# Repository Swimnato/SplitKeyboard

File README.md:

# SplitKeyboard
Split keyboard with rotary encoder using the Nice!Nano V2

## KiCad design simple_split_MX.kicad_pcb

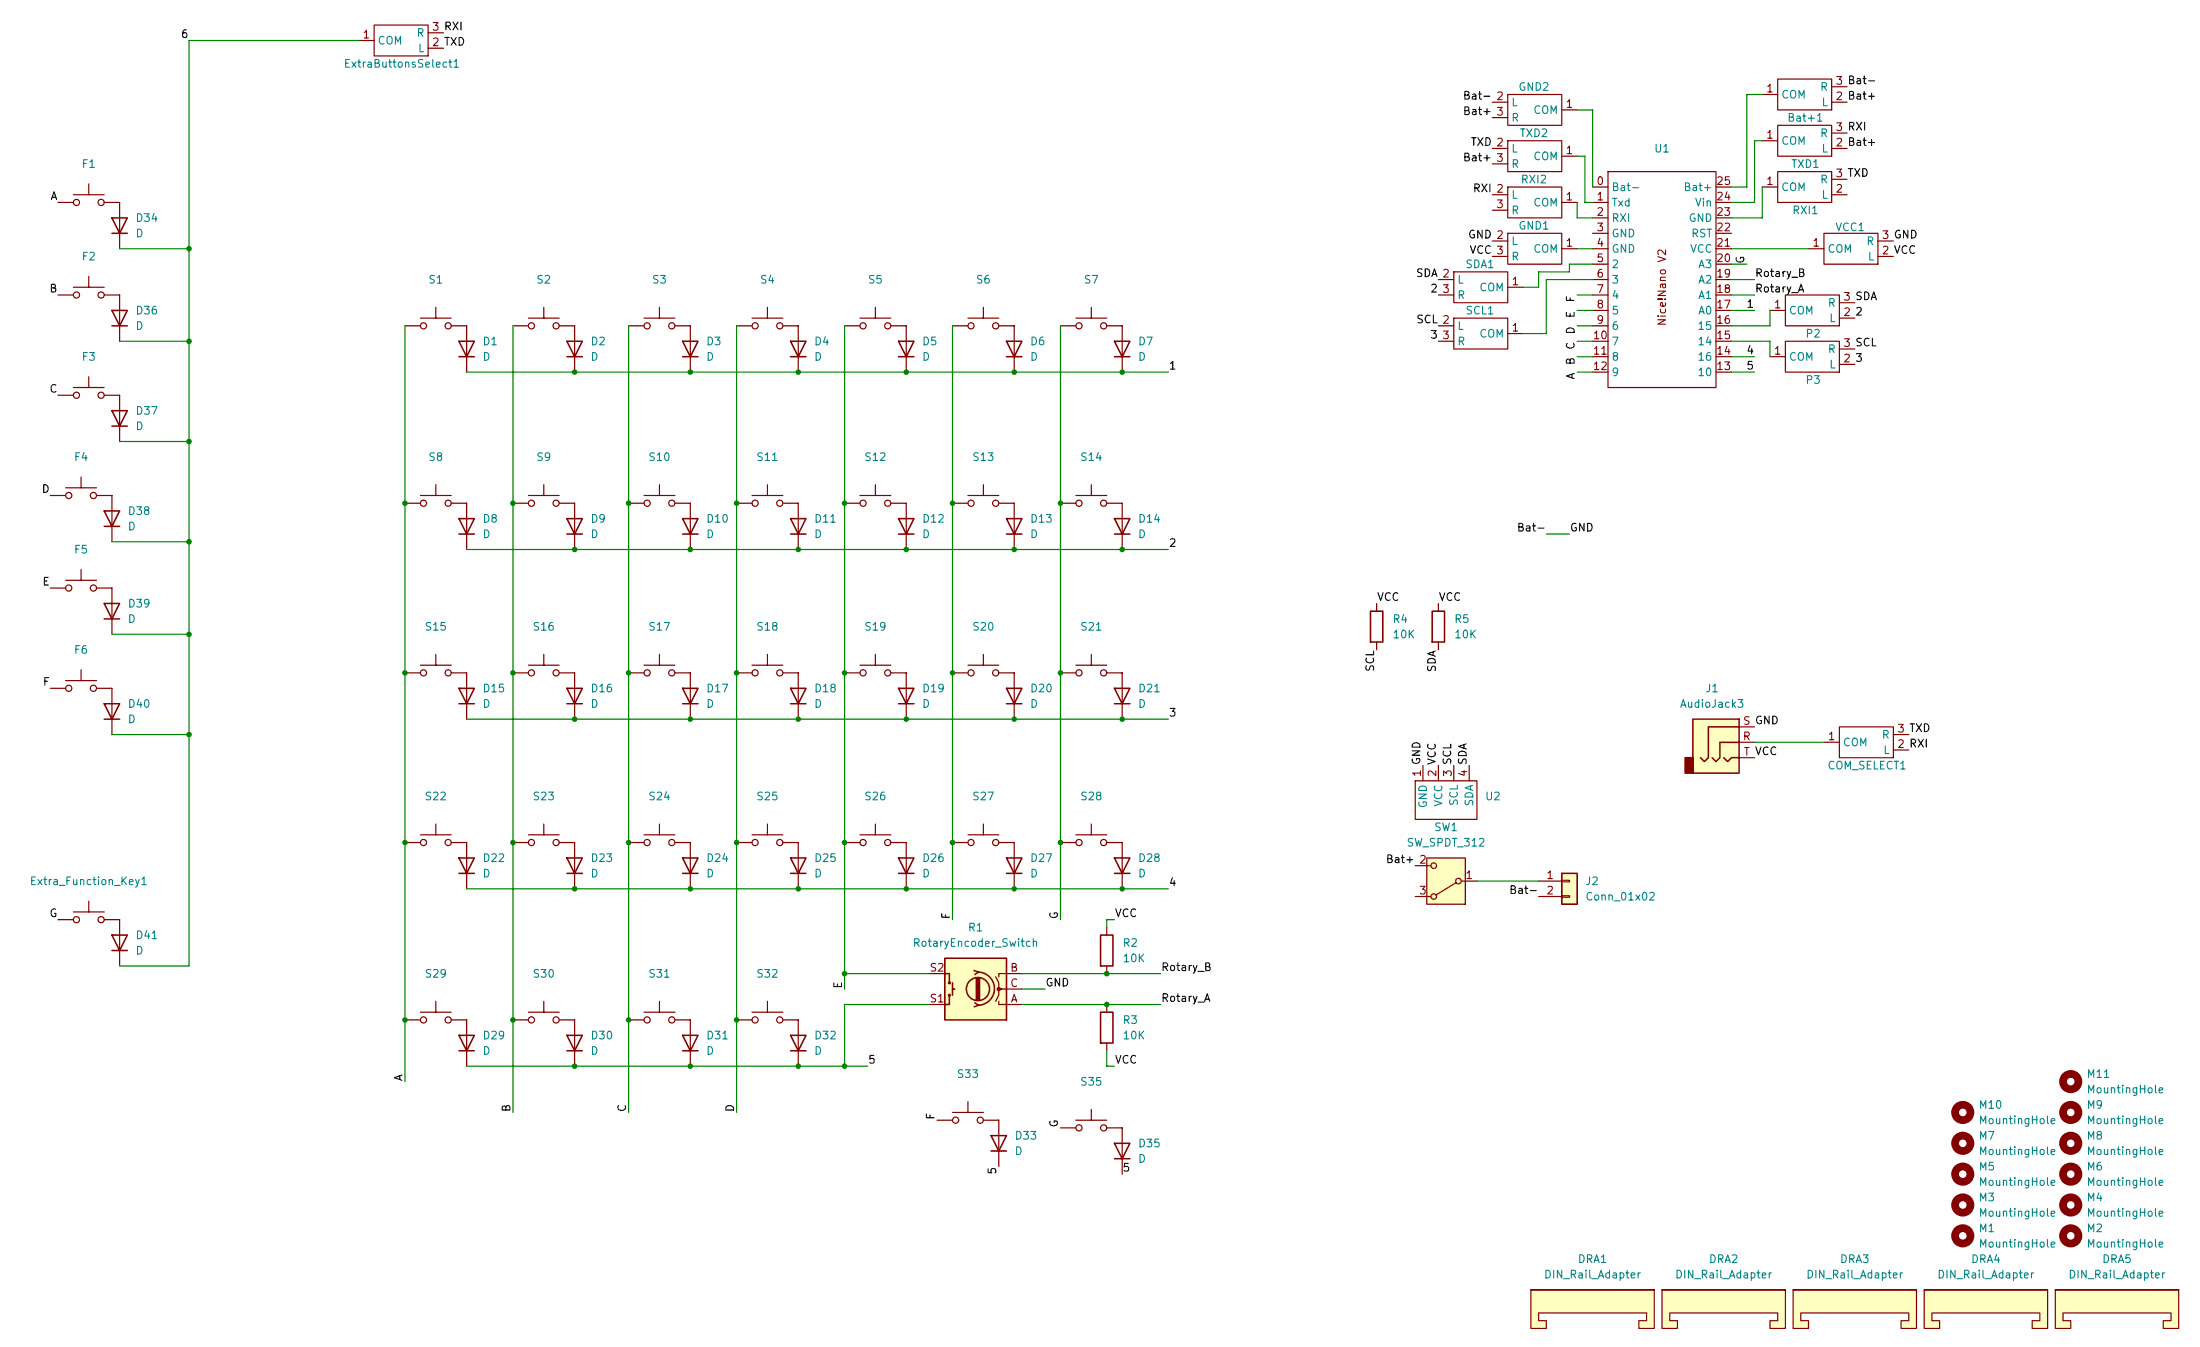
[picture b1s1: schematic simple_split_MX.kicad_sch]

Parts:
Bat+1: Side Indicator - Improved
COM_SELECT1: Side Indicator - Improved
D1, D2, D3, D4, D5, D6, D7, D8, D9, D10, D11, D12, D13, D14, D15, D16, D17, D18, D19, D20, D21, D22, D23, D24, D25, D26, D27, D28, D29, D30, D31, D32, D33, D34, D35, D36, D37, D38, D39, D40, D41: D; reversable_diode
DRA1, DRA2, DRA3, DRA4, DRA5: DIN_Rail_Adapter; Stabilizer_MX_2u
ExtraButtonsSelect1: Side Indicator - Improved
Extra_Function_Key1: Kailh_socket_MX_reversible
F1, F2, F3, F4, F5, F6: Kailh_socket_MX_reversible
GND1, GND2: Side Indicator - Improved
J1: AudioJack3; Jack_3.5mm_CUI_SJ1-3533NG_Horizontal Reversable
J2: Conn_01x02; JST_EH_S2B-EH_1x02_P2.50mm_Horizontal
M1, M2, M3, M4, M5, M6, M7, M8, M9, M10, M11: MountingHole; MountingHole_2.2mm_M2
P2, P3: Side Indicator - Improved
R1: RotaryEncoder_Switch; RotaryEncoder_Alps_EC11E-Switch_Vertical_H20mm
R2, R3, R4, R5: 10K; R_Axial_DIN0204_L3.6mm_D1.6mm_P7.62mm_Horizontal
RXI1, RXI2: Side Indicator - Improved
S1, S2, S3, S4, S5, S6, S7, S8, S9, S10, S11, S12, S13, S14, S15, S16, S17, S18, S19, S20, S21, S22, S23, S24, S25, S26, S27, S28, S29, S30, S31, S32, S33, S35: Kailh_socket_MX_reversible
SCL1: Side Indicator - Improved
SDA1: Side Indicator - Improved
SW1: SW_SPDT_312; SW_Slide_SPDT_Angled_CK_OS102011MA1Q
TXD1, TXD2: Side Indicator - Improved
U1: Nice!NanoV2
U2: Screen
VCC1: Side Indicator - Improved

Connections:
/1: D1.1 (K), D2.1 (K), D3.1 (K), D4.1 (K), D5.1 (K), D6.1 (K), D7.1 (K), U1.17 (A0)
/2: D8.1 (K), D9.1 (K), D10.1 (K), D11.1 (K), D12.1 (K), D13.1 (K), D14.1 (K), P2.2 (L), SDA1.3 (R)
/3: D15.1 (K), D16.1 (K), D17.1 (K), D18.1 (K), D19.1 (K), D20.1 (K), D21.1 (K), P3.2 (L), SCL1.3 (R)
/4: D22.1 (K), D23.1 (K), D24.1 (K), D25.1 (K), D26.1 (K), D27.1 (K), D28.1 (K), U1.14 (16)
/5: D29.1 (K), D30.1 (K), D31.1 (K), D32.1 (K), D33.1 (K), D35.1 (K), R1.S1, U1.13 (10)
/6: D34.1 (K), D36.1 (K), D37.1 (K), D38.1 (K), D39.1 (K), D40.1 (K), D41.1 (K), ExtraButtonsSelect1.1 (COM)
/A: F1.1 (A), S1.1 (A), S8.1 (A), S15.1 (A), S22.1 (A), S29.1 (A), U1.12 (9)
/B: F2.1 (A), S2.1 (A), S9.1 (A), S16.1 (A), S23.1 (A), S30.1 (A), U1.11 (8)
/Bat+: Bat+1.2 (L), GND2.3 (R), SW1.2 (C), TXD1.2 (L), TXD2.3 (R)
/Bat-: Bat+1.3 (R), GND1.2 (L), GND2.2 (L), J1.S, J2.2, R1.C, U2.1 (GND), VCC1.3 (R)
/C: F3.1 (A), S3.1 (A), S10.1 (A), S17.1 (A), S24.1 (A), S31.1 (A), U1.10 (7)
/D: F4.1 (A), S4.1 (A), S11.1 (A), S18.1 (A), S25.1 (A), S32.1 (A), U1.9 (6)
/E: F5.1 (A), R1.S2, S5.1 (A), S12.1 (A), S19.1 (A), S26.1 (A), U1.8 (5)
/F: F6.1 (A), S6.1 (A), S13.1 (A), S20.1 (A), S27.1 (A), S33.1 (A), U1.7 (4)
/G: Extra_Function_Key1.1 (A), S7.1 (A), S14.1 (A), S21.1 (A), S28.1 (A), S35.1 (A), U1.20 (A3)
/RXI: COM_SELECT1.2 (L), ExtraButtonsSelect1.3 (R), RXI2.2 (L), TXD1.3 (R)
/Rotary_A: R1.A, R3.1, U1.18 (A1)
/Rotary_B: R1.B, R2.2, U1.19 (A2)
/SCL: P3.3 (R), R4.2, SCL1.2 (L), U2.3 (SCL)
/SDA: P2.3 (R), R5.2, SDA1.2 (L), U2.4 (SDA)
/TXD: COM_SELECT1.3 (R), ExtraButtonsSelect1.2 (L), RXI1.3 (R), TXD2.2 (L)
/VCC: GND1.3 (R), J1.T, R2.1, R3.2, R4.1, R5.1, U2.2 (VCC), VCC1.2 (L)
unnamed: Bat+1.1 (COM), U1.25 (Bat+)
unnamed: COM_SELECT1.1 (COM), J1.R
unnamed: D1.2 (A), S1.2 (B)
unnamed: D2.2 (A), S2.2 (B)
unnamed: D3.2 (A), S3.2 (B)
unnamed: D4.2 (A), S4.2 (B)
unnamed: D5.2 (A), S5.2 (B)
unnamed: D6.2 (A), S6.2 (B)
unnamed: D7.2 (A), S7.2 (B)
unnamed: D8.2 (A), S8.2 (B)
unnamed: D9.2 (A), S9.2 (B)
unnamed: D10.2 (A), S10.2 (B)
unnamed: D11.2 (A), S11.2 (B)
unnamed: D12.2 (A), S12.2 (B)
unnamed: D13.2 (A), S13.2 (B)
unnamed: D14.2 (A), S14.2 (B)
unnamed: D15.2 (A), S15.2 (B)
unnamed: D16.2 (A), S16.2 (B)
unnamed: D17.2 (A), S17.2 (B)
unnamed: D18.2 (A), S18.2 (B)
unnamed: D19.2 (A), S19.2 (B)
unnamed: D20.2 (A), S20.2 (B)
unnamed: D21.2 (A), S21.2 (B)
unnamed: D22.2 (A), S22.2 (B)
unnamed: D23.2 (A), S23.2 (B)
unnamed: D24.2 (A), S24.2 (B)
unnamed: D25.2 (A), S25.2 (B)
unnamed: D26.2 (A), S26.2 (B)
unnamed: D27.2 (A), S27.2 (B)
unnamed: D28.2 (A), S28.2 (B)
unnamed: D29.2 (A), S29.2 (B)
unnamed: D30.2 (A), S30.2 (B)
unnamed: D31.2 (A), S31.2 (B)
unnamed: D32.2 (A), S32.2 (B)
unnamed: D33.2 (A), S33.2 (B)
unnamed: D34.2 (A), F1.2 (B)
unnamed: D35.2 (A), S35.2 (B)
unnamed: D36.2 (A), F2.2 (B)
unnamed: D37.2 (A), F3.2 (B)
unnamed: D38.2 (A), F4.2 (B)
unnamed: D39.2 (A), F5.2 (B)
unnamed: D40.2 (A), F6.2 (B)
unnamed: D41.2 (A), Extra_Function_Key1.2 (B)
unnamed: GND1.1 (COM), U1.4 (GND)
unnamed: GND2.1 (COM), U1.0 (Bat-)
unnamed: J2.1, SW1.1 (B)
unnamed: P2.1 (COM), U1.16 (15)
unnamed: P3.1 (COM), U1.15 (14)
unnamed: RXI1.1 (COM), U1.23 (GND)
unnamed: RXI2.1 (COM), U1.2 (RXI)
unnamed: SCL1.1 (COM), U1.6 (3)
unnamed: SDA1.1 (COM), U1.5 (2)
unnamed: TXD1.1 (COM), U1.24 (Vin)
unnamed: TXD2.1 (COM), U1.1 (Txd)
unnamed: U1.21 (VCC), VCC1.1 (COM)

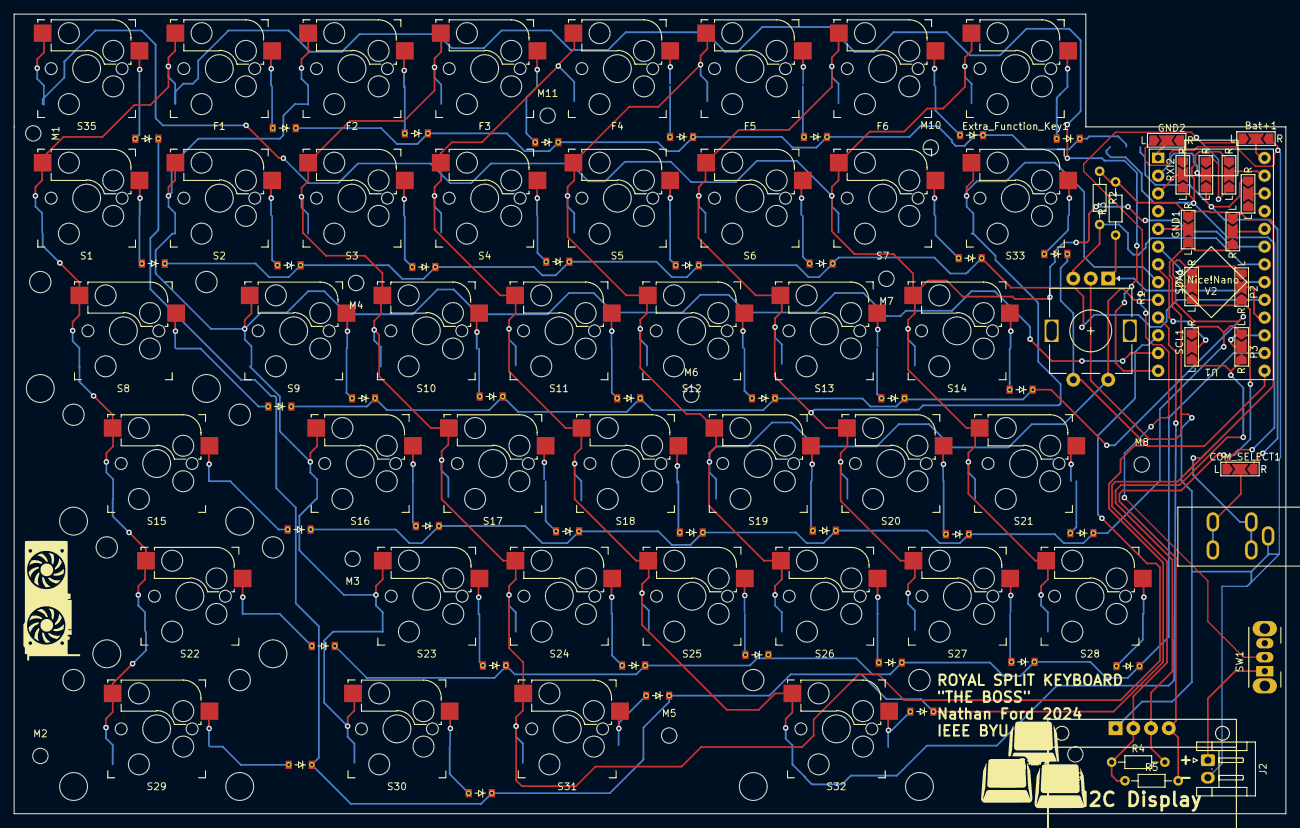
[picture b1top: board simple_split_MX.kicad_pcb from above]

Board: 2 copper layers, 182.1 x 114.5 mm, 122 parts (1 on the bottom side), 77 nets.

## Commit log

2024-11-03 added 7 keys
    14 in total between two sides
    -F1-12
    -2 multipurpose
2024-11-03 Finished V6
2024-11-08 Finished Routing for MX switches
    - Ran DRC in KiCad
    - Ran JLDFC and I comply with all but THT to SMD spacing, because the side indication jumpers "aren't ideal" because there could be solder wicking, but I will just be careful when assembling the boar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
2024-11-08 updated board to remove unused vias
2024-11-08 Fixed exposed trace
2024-11-14 added custom silkscreen
2024-11-15 added a new Image
2024-11-21 fixed major problem
2024-11-21 fixed problem
2024-11-22 updated pcb
2025-01-17 cleaning up a bit
2025-01-26 added/updated 3d files
2025-02-02 added labels
